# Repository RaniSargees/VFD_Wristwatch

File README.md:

# VFD_Wristwatch
Plans for a wristwatch using the IVL2-7/5 Vacuum display tube.

---

# this project is semi-functional but incomplete
it worked briefly but the io expander kept exploding, so I scrapped this. i've uploaded the in-progress firmware for reference only.

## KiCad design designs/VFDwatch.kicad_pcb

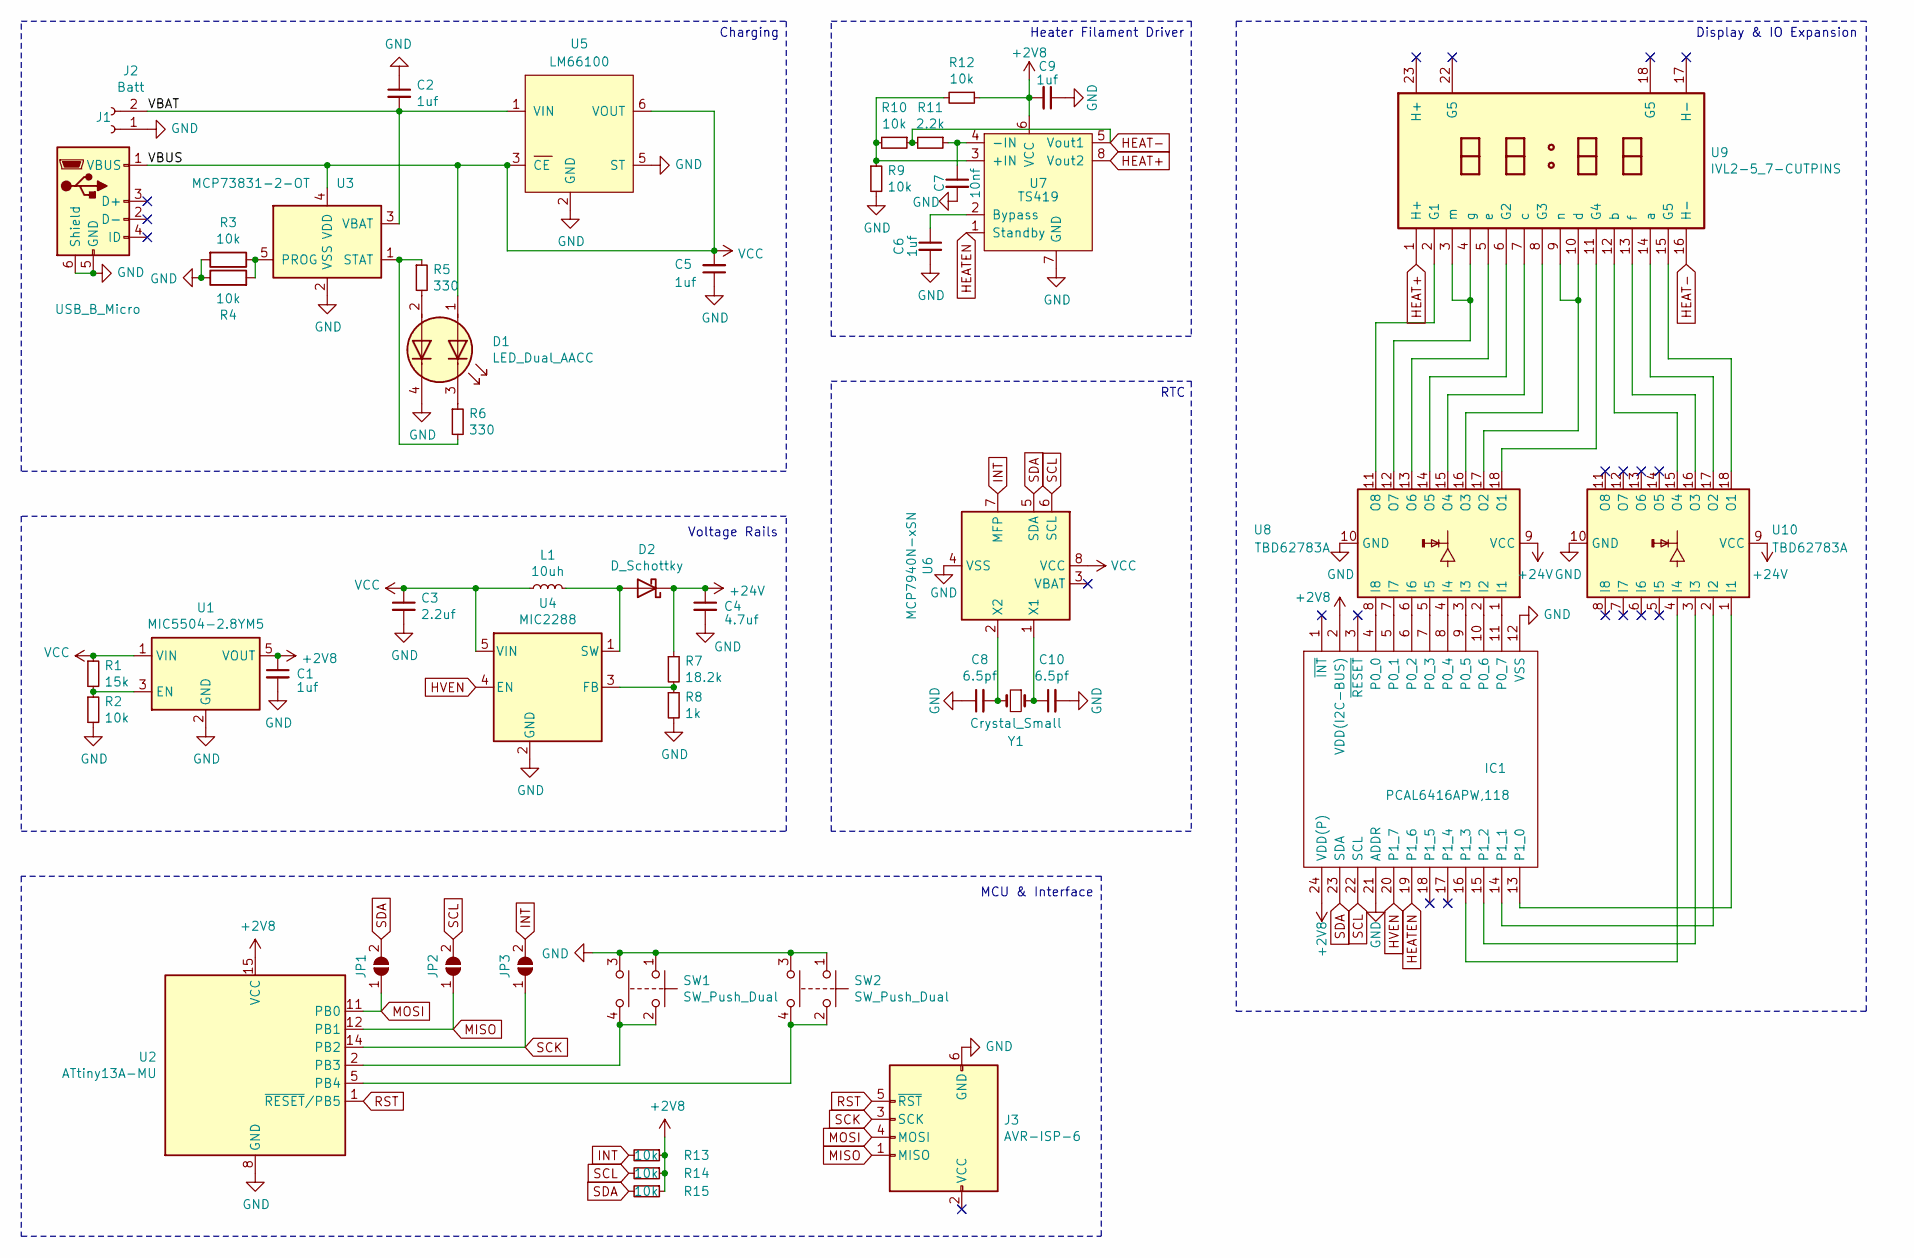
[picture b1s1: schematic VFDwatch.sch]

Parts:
C1, C2, C5, C6, C9: 1uf; C_0402_1005Metric_Pad0.74x0.62mm_HandSolder
C3: 2.2uf; C_0603_1608Metric_Pad1.05x0.95mm_HandSolder
C4: 4.7uf; C_0805_2012Metric
C7: 10nf; C_0603_1608Metric_Pad1.05x0.95mm_HandSolder
C8, C10: 6.5pf; C_0603_1608Metric_Pad1.05x0.95mm_HandSolder
D1: LED_Dual_AACC; 1616LED
D2: D_Schottky; D_SOD-123F
IC1: PCAL6416APW,118; SOP65P640X110-24N; Mouser Part Number 771-PCAL6416APW118
J1: USB_B_Micro; 101181920001LF
J2: Batt; PinHeader_1x02_P2.54mm_Vertical
J3: AVR-ISP-6; PinHeader_2x03_P2.54mm_Vertical
JP1, JP2, JP3: SolderJumper_2_Open; SolderJumper-2_P1.3mm_Open_Pad1.0x1.5mm
L1: 10uh; L_1210_3225Metric_Pad1.42x2.65mm_HandSolder
R1: 15k; R_0402_1005Metric_Pad0.72x0.64mm_HandSolder
R2, R3, R4, R9, R10, R12, R13, R14, R15: 10k; R_0402_1005Metric_Pad0.72x0.64mm_HandSolder
R5, R6: 330; R_0603_1608Metric_Pad0.98x0.95mm_HandSolder
R7: 18.2k; R_0603_1608Metric_Pad0.98x0.95mm_HandSolder
R8: 1k; R_0603_1608Metric_Pad0.98x0.95mm_HandSolder
R11: 2.2k; R_0603_1608Metric_Pad0.98x0.95mm_HandSolder
SW1, SW2: SW_Push_Dual; PTS647SM50SMTR2LFS
U1: MIC5504-2.8YM5; SOT-23-5
U2: ATtiny13A-MU; QFN-20-1EP_4x4mm_P0.5mm_EP2.6x2.6mm
U3: MCP73831-2-OT; SOT-23-5
U4: MIC2288; TSOT-23-5
U5: LM66100; SOT-363_SC-70-6
U6: MCP7940N-xSN; SOIC-8_3.9x4.9mm_P1.27mm
U7: TS419; miniSO-8
U8, U10: TBD62783A; SOP-18_7x12.5mm_P1.27mm
U9: IVL2-5_7-CUTPINS; IVL2-7_5-CUTPINS
Y1: Crystal_Small; TestPoint_2Pads_Pitch2.54mm_Drill0.8mm

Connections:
+2V8: C1.1, C9.2, IC1.2 (VDD(I2C-BUS)), IC1.24 (VDD(P)), R12.1, R13.1, R14.1, R15.1, U1.5 (VOUT), U2.15 (VCC), U7.6 (VCC)
+24V: C4.1, D2.1 (K), R7.1, U8.9 (VCC), U10.9 (VCC)
/VBAT: C2.2, J2.2, U3.3 (VBAT), U5.1 (VIN)
GND: C1.2, C2.1, C3.2, C4.2, C5.1, C6.2, C7.2, C8.1, C9.1, C10.2, D1.4 (K2), IC1.12 (VSS), IC1.21 (ADDR), J1.5 (GND), J1.6 (Shield), J2.1, J3.6 (GND), R2.2, R3.2, R4.1, R8.2, R9.2, SW1.1, SW1.3, SW2.1, SW2.3, U1.2 (GND), U2.8 (GND), U2.21 (GND), U3.2 (VSS), U4.2 (GND), U5.2 (GND), U5.5 (ST), U6.4 (VSS), U7.7 (GND), U8.10 (GND), U10.10 (GND)
HEAT+: U7.8 (Vout2), U9.1 (H+)
HEAT-: R10.1, R11.2, U7.5 (Vout1), U9.16 (H-)
HEATEN: IC1.19 (P1_6), U7.1 (Standby)
HVEN: IC1.20 (P1_7), U4.4 (EN)
INT: JP3.2 (B), R13.2, U6.7 (MFP)
MISO: J3.1 (MISO), JP2.1 (A), U2.12 (PB1)
MOSI: J3.4 (MOSI), JP1.1 (A), U2.11 (PB0)
unnamed: C6.1, U7.2 (Bypass)
unnamed: C7.1, R11.1, U7.4 (-IN)
unnamed: C8.2, U6.2 (X2), Y1.2
unnamed: C10.1, U6.1 (X1), Y1.1
unnamed: D1.2 (A2), R5.2
unnamed: D1.3 (K1), R6.1
unnamed: D2.2 (A), L1.2, U4.1 (SW)
unnamed: IC1.4 (P0_0), U8.8 (I8)
unnamed: IC1.5 (P0_1), U8.7 (I7)
unnamed: IC1.6 (P0_2), U8.6 (I6)
unnamed: IC1.7 (P0_3), U8.5 (I5)
unnamed: IC1.8 (P0_4), U8.4 (I4)
unnamed: IC1.9 (P0_5), U8.3 (I3)
unnamed: IC1.10 (P0_6), U8.2 (I2)
unnamed: IC1.11 (P0_7), U8.1 (I1)
unnamed: IC1.13 (P1_0), U10.1 (I1)
unnamed: IC1.14 (P1_1), U10.2 (I2)
unnamed: IC1.15 (P1_2), U10.3 (I3)
unnamed: IC1.16 (P1_3), U10.4 (I4)
unnamed: R1.2, R2.1, U1.3 (EN)
unnamed: R3.1, R4.2, U3.5 (PROG)
unnamed: R5.1, R6.2, U3.1 (STAT)
unnamed: R7.2, R8.1, U4.3 (FB)
unnamed: R9.1, R10.2, R12.2, U7.3 (+IN)
unnamed: SW1.2, SW1.4, U2.2 (PB3)
unnamed: SW2.2, SW2.4, U2.5 (PB4)
unnamed: U8.11 (O8), U9.2 (G1)
unnamed: U8.12 (O7), U9.3 (m), U9.4 (g)
unnamed: U8.13 (O6), U9.5 (e)
unnamed: U8.14 (O5), U9.6 (G2)
unnamed: U8.15 (O4), U9.7 (c)
unnamed: U8.16 (O3), U9.8 (G3)
unnamed: U8.17 (O2), U9.9 (n), U9.10 (d)
unnamed: U8.18 (O1), U9.11 (G4)
unnamed: U9.12 (b), U10.15 (O4)
unnamed: U9.13 (f), U10.16 (O3)
unnamed: U9.14 (a), U10.17 (O2)
unnamed: U9.15 (G5), U10.18 (O1)
RST: J3.5 (~RST), U2.1 (~RESET~/PB5)
SCK: J3.3 (SCK), JP3.1 (A), U2.14 (PB2)
SCL: IC1.22 (SCL), JP2.2 (B), R14.2, U6.6 (SCL)
SDA: IC1.23 (SDA), JP1.2 (B), R15.2, U6.5 (SDA)
VCC: C3.1, C5.2, D1.1 (A1), J1.1 (VBUS), L1.1, R1.1, U1.1 (VIN), U3.4 (VDD), U4.5 (VIN), U5.3 (CE), U5.6 (VOUT), U6.8 (VCC)

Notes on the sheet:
Charging
Voltage Rails
Display & IO Expansion
Heater Filament Driver
RTC
MCU & Interface

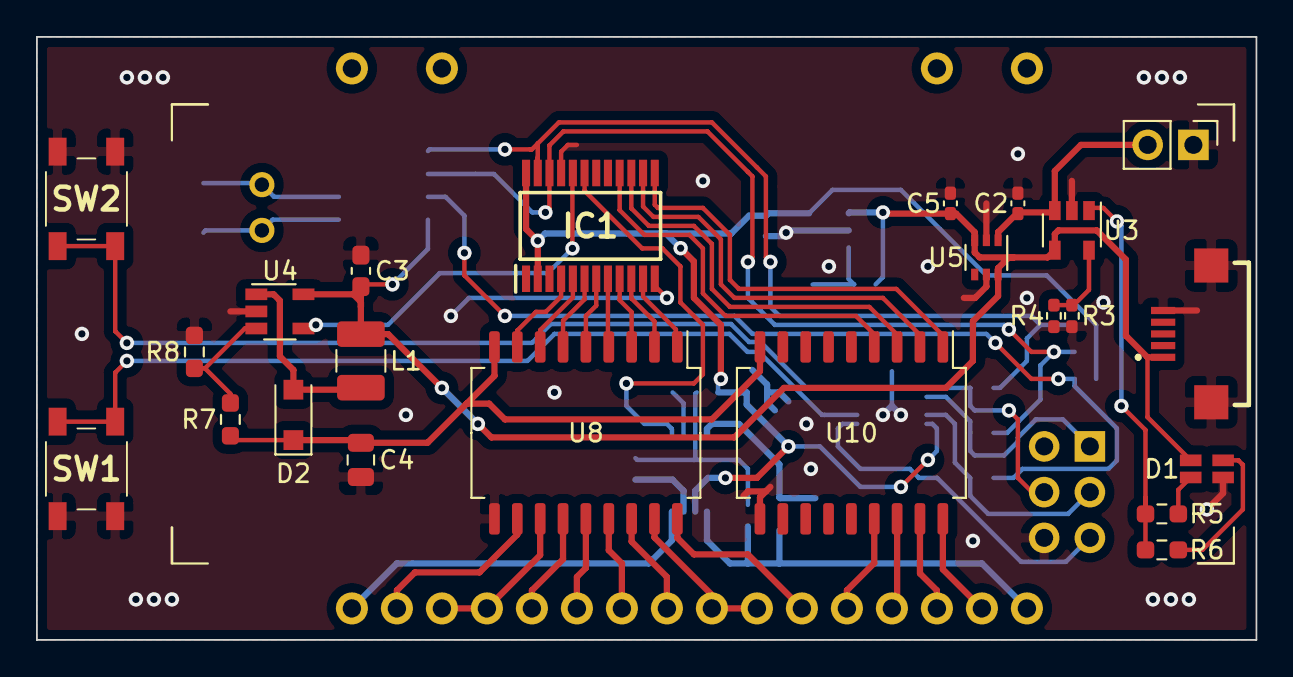
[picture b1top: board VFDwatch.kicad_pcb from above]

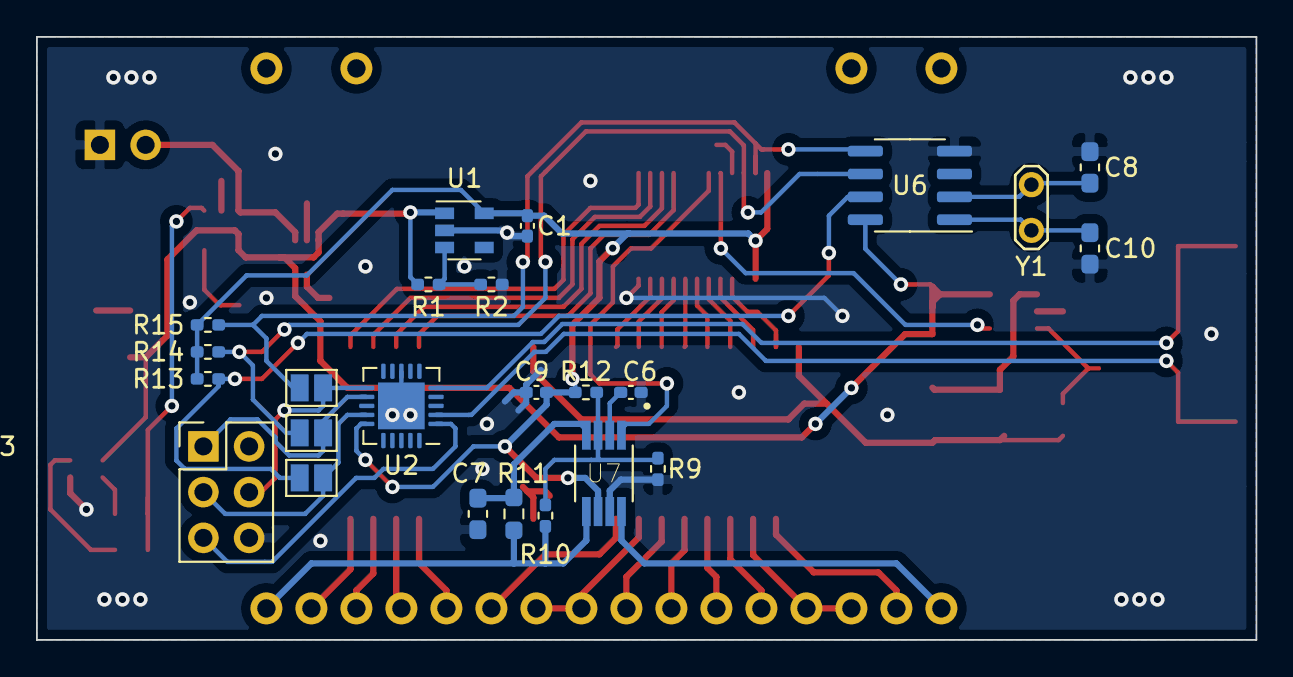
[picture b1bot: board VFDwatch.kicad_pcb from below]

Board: 2 copper layers, 67.8 x 33.5 mm, 48 parts (24 on the bottom side), 54 nets.

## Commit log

2021-02-02 Add PCB designs
2025-02-18 upload firmware, scrap project
